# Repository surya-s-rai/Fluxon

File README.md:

# Fluxon
## Project Overview

<br><br>

__Fluxon__ - A PVDF Sensor based Flux logger that collects collision data, a especailly designed payload for CubeSat\
Collects useful data values once embedded on side walls of the satellite as shown in the Zine page above.
<br><br>

 ## Why I made this
 I made this project for a hardware hackathon called fallout organised by [Hack Club](https://github.com/hackclub), and particularly choosed to make this Iot device as i wanted to make a prototype of something real used in spacecrafts.
 ## Why it is relevant
 * Scientific value: Current flux models like [ORDEM](https://orbitaldebris.jsc.nasa.gov/modeling/ordem.html) and [MASTER](https://conference.sdo.esoc.esa.int/proceedings/sdc3/paper/92/SDC3-paper92.pdf) rely mainly on simulations and ground based radar data. A physical sensor mounted on small satellite misson measures impact data better than any simulation can replicate.
 * Cost effective: Commercial impact detectors used in experiments cost thousands of dollars, whereas Fluxon is an open source, low cost substitute PCB board.
 * Mechanical compatibility with real CubeSats: The 60mm x 60mm form factor matches the standard face panel dimensions of CubeSat.
 * Solar powered: The SPV1040 maximum power point tracker(MPPT) harvests energy form solar cell and charges the supercapacitor which reduces the burden of holding a separate battery into a small scale satellite.
 * Mass-frequency distribution: This statistically relevant distribution is obtained from the measured peak voltage which is proportional to mechanical impulse delivered on the aluminium face panel.
 * Flux density: The DS3231 which is a highly accurate real time clock(RTC) helps us to measure particle flux in units of particles per area per second. Flux density is meaningful beacause it varies with orbital altitude, inclination and the time of year(the earth's debris envionment is not uniform).
 * Impact direction: If we embed Fluxon on each face panel of CubeSat, we can calculate angular distribution of impact using parameters like time difference between sensor pairs, speed of sound in aluminium (6320 m/s) and known sensor geometry.
 ## How it works
 The payload is mainly divided into 4 major chunks-
 ### 1. Sensor Frontend (Impact Detection Hardware)
Converts tiny charge generted by the peizoelectric sensors into a measurable voltage.

 ### 2. Signal Conditioning
 Gives Amplified, noise reduced input for Microcontroller unit. 

 ### 3. Microcontroller and Firmware
 Processes sensor data and uses specific codes that brigdes the hardware requirements.

 ### 4. Data Storage System
 Uses W25Q128JV to store collected events.

 ## What's inside this folder
 # PCB Files:
 `* flux logger project.kicad_sch`-contains an illustrative layout of parts and wires used in the project

 `* flux logger project.kicad_pcb`\-The actual pcb layout with all components placed and routed

 `* BOM updated1.xlsx`-Bill of materials with all parts

 # Firware:
 `* Firmware` folder contains hardware specific C codes for parts to operate
 
 # Other files
 `* Flux logger project.kicad_pro`-links `kicad_sch` and `kicad_pcb` files.
 
 `ChargeAmplifier.kicad_sch`,`TPS_Vin.kicad_sch` and`Thre_comp.Kicad_sch` are sub parts of main schema file i.e. `flux logger project.Kicad_sch` 
 ## Build Guide
 1. Replicate the Repository into your local environment
 
 2. View `flux logger project.kicad_sch`,`flux logger project.kicad_pcb` along with the pcb's 3D View on [Kicad](https://www.kicad.org/)
 
 3. PCB Assembly\
 Solder components in the following order:
 resistors and capacitors,Sensor, ADA4530-1, MSP430, W25Q128JV, Connectors and testpoints

 4. Check High Impedance Areas
 Ensure gaurd ring surrounding Amplifier and Sensor input traces.
 Also, keep sensor input clean and isolated.

 5. Power Supply Check
 Apply 3.3V Supply according to `.kicad_sch` file and verify 3.3V rail across each IC.

 6. Firware Installation

 #### Required Software
 * Visual Studio Code Editor
 * PlatformIO Extension
 * Texas Instruments MSP430 Toolchain

 7. Build and Upload Firware

 * Open Firmware folder and run `pio run` on CLI

 * Use upload Button on PlatformIO in order to upload the programme

## BOM
| Value              | Reference                                  | Footprint                                                                          | Qty | Unit Price     | Total Price    | URL                                                                                                                                                                                                                                                                                                                            |
|--------------------|--------------------------------------------|------------------------------------------------------------------------------------|-----|----------------|----------------|--------------------------------------------------------------------------------------------------------------------------------------------------------------------------------------------------------------------------------------------------------------------------------------------------------------------------------|
| 100nf              | C1,C2,C3,C5,C6,C7,C13,C15,C16              | Capacitor_SMD:C_0805_2012Metric                                                    | 9   | 1rs            | 9rs            | https://projectpoint.in/index.php?route=product/product&product_id=636107122                                                                                                                                                                                                                                                   |
| 1uf                | C17,C12                                    | Capacitor_SMD:C_0805_2012Metric                                                    | 2   | 2.09rs         | 4.18rs         | https://robu.in/product/1uf-1000nf-50v-capacitor-0805-smd-package-pack-of-10/                                                                                                                                                                                                                                                  |
| 10uF               | C9,C11,C8,C18                              | Capacitor_SMD:C_0805_2012Metric                                                    | 4   | 3.44rs         | 13.76rs        | https://robu.in/product/grm21bb31c106me15l-murata-electronics-16v-10uf-%C2%B120-0805-multilayer-ceramic-capacitors-mlcc-smd-smt-rohs/                                                                                                                                                                                          |
| 22uF               | C10,C14                                    | Capacitor_SMD:C_1206_3216Metric                                                    | 2   | 0.98rs         | 1.96rs         | https://robu.in/product/cs3216x5r226m6r3nri-samwha-6-3v-22uf-x5r-%C2%B120-1206-multilayer-ceramic-capacitors-mlcc-smd-smt-rohs/                                                                                                                                                                                                |
| 10pf               | Cf1                                        | Resistor_SMD:R_0603_1608Metric                                                     | 1   | 0.92rs         | 0.92rs         | https://robu.in/product/10pf-0603-surface-mount-multilayer-ceramic-capacitor-pack-of-50/                                                                                                                                                                                                                                       |
| 100mf              | S_Cap1                                     | Capacitor_THT:CP_Radial_D10.0mm_P5.00mm                                            | 1   | 99.00rs        | 99.00rs        | https://robu.in/product/0-1f-5-5v-dip-super-capacitor/                                                                                                                                                                                                                                                                         |
| Conn_01x04         | J1                                         | Connector_PinHeader_2.54mm:PinHeader_1x02_P2.54mm_Vertical                         | 2   | 1.50rs         |         3.00rs | https://ifuturetech.org/product/xh2-54-2p-curved-needle-connector-holder-2-54mm-white/                                                                                                                                                                                                                                         |
| 22uH               | L2                                         | Inductor_SMD:L_7.3x7.3_H4.5                                                        | 1   | 8.00rs         | 8.00rs         | https://robu.in/product/68mm-22%C2%B5h-dip-power-inductor-pack-of-5/?gad_source=4&gad_campaignid=17427802703&gbraid=0AAAAADvLFWcfg8oALnufuCDn7QS7Yxsgw&gclid=CjwKCAjw9NjRBhATEiwA_p2J8UuSwcfA2Lr5wrlX0WQkwEzMOyO9Nd1P-ll7UbZbTWQCKsbAUmGBtxoCC_MQAvD_BwE                                                                       |
| 10K                | RV2                                        | Potentiometer_THT:Potentiometer_Bourns_3296W_Vertical                              | 1   | 14.70rs        | 14.70rs        | https://projectpoint.in/index.php?route=product/product&product_id=1500453261                                                                                                                                                                                                                                                  |
| 4.7K               | R1,R3                                      | Resistor_SMD:R_0805_2012Metric                                                     | 2   | 0.44rs         | 0.88rs         | https://robu.in/product/yageo-4-7k-ohm-1-4w-0805-surface-mount-resistor-pack-of-50/?gad_source=4&gad_campaignid=17427802703&gbraid=0AAAAADvLFWcfg8oALnufuCDn7QS7Yxsgw&gclid=CjwKCAjw9NjRBhATEiwA_p2J8W7dYQrZnCsdsWutgfi2JOE-1O_Ukj8FJljlKnBzD6cBGYgiVhon4hoCGU4QAvD_BwE                                                        |
| 100M               | R2                                         | Resistor_SMD:R_1206_3216Metric                                                     | 1   | 84.75rs        | 84.75rs        | https://srkelectronics.in/product/1-mega-ohm-1206-smd-resistor-cfr-pack-of-100/                                                                                                                                                                                                                                                |
| 470K               | R10                                        | Resistor_SMD:R_0603_1608Metric                                                     | 1   | 8.00rs         | 8.00rs         | https://quartzcomponents.com/products/470k-ohm-0603-package-1-10w-smd-resistor-5-tolerance-pack-of-20-pieces?variant=44678130565354&country=IN&currency=INR&utm_medium=product_sync&utm_source=google&utm_content=sag_organic&utm_campaign=sag_organic&srsltid=AfmBOooqJKQhW7YbzG5QFEy0RA-DWadXqpZfb886LD__9LHmBCOOGl79qMo     |
| 10K                | R5,R8,R4,R11                               | Resistor_SMD:R_1206_3216Metric                                                     | 4   | 0.69rs         |       2.76rs   | https://robu.in/product/10k-ohm-1-4w-1206-surface-mount-chip-resistor-pack-of-100/?gad_source=4&gad_campaignid=17427802703&gbraid=0AAAAADvLFWcfg8oALnufuCDn7QS7Yxsgw&gclid=CjwKCAjw9NjRBhATEiwA_p2J8YndTZpSAUk0yIELKsWgMxWpWZsCg3WXOXNIa_TPXrjVBX5Mqxgn4xoChh0QAvD_BwE                                                         |
| 13.3K              | R6                                         | Resistor_SMD:R_1206_3216Metric                                                     | 1   | 1.70rs         | 1.70rs         | https://projectpoint.in/index.php?route=product/product&product_id=499506064082                                                                                                                                                                                                                                                |
| 47k                | R7                                         | Resistor_SMD:R_1206_3216Metric                                                     | 1   | 1.70rs         | 1.70rs         | https://projectpoint.in/index.php?route=product/product&product_id=501263610758                                                                                                                                                                                                                                                |
| 9.1K               | R9                                         | Resistor_SMD:R_1206_3216Metric                                                     | 1   | 1.70rs         | 1.70rs         | https://projectpoint.in/index.php?route=product/product&product_id=502522332251                                                                                                                                                                                                                                                |
| 220K               | RST1                                       | Resistor_SMD:R_1206_3216Metric                                                     | 1   | 1.70rs         | 1.70rs         | https://projectpoint.in/index.php?route=product/product&product_id=501903421507                                                                                                                                                                                                                                                |
| 100K               | RST2                                       | Resistor_SMD:R_1206_3216Metric                                                     | 1   | 0.79rs         | 0.79rs         | https://robu.in/product/100k-ohm-1-4w-1206-surface-mount-chip-resistor-pack-of-100/?gad_source=4&gad_campaignid=17427802703&gbraid=0AAAAADvLFWcd2632Ty4S6PMw-fukdNsD1&gclid=CjwKCAjwl97RBhBWEiwAa9rbXZb4d1umDK0ptoRG9JBTgPPU3BVFfywxlvYmKyawWVLWZqEBT12_WRoCiUYQAvD_BwE                                                        |
| 1M                 | R_hys1                                     | Resistor_SMD:R_0603_1608Metric                                                     | 1   | 9.00rs         | 9.00rs         | https://quartzcomponents.com/products/yageo-1m-ohm-0603-package-1-10w-smd-resistor-1-tolerance-pack-of-20-pieces?variant=45952342458602&country=IN&currency=INR&utm_medium=product_sync&utm_source=google&utm_content=sag_organic&utm_campaign=sag_organic&srsltid=AfmBOop2TJlavxmk_Py0tepDthLo-4WGt6L3SB3oAG36sDNxWqzsWehiqpk |
| 1K                 | R12                                        | Resistor_SMD:R_1206_3216Metric                                                     | 1   | 0.65rs         | 0.65rs         | https://robu.in/product/1k-ohm-1-4w-1206-surface-mount-chip-resistor-pack-of-100/?gad_source=4&gad_campaignid=17427802703&gbraid=0AAAAADvLFWcd2632Ty4S6PMw-fukdNsD1&gclid=CjwKCAjwl97RBhBWEiwAa9rbXZhhZrsnIQ2GC6qdmROeP4HSg4zL3TrdbdUty2efHun2CRlimZtfgBoCH5kQAvD_BwE                                                          |
| PDVF Sensor        | S1                                         | Connector_JST:JST_PH_B2B-PH-K_1x02_P2.00mm_Vertical                                | 1   | 42rs           | 42rs           | https://www.flyrobo.in/10cm-2pin-jst-male-female-plug-connector-plug?tracking=ads&srsltid=AfmBOorg-c1t1ZMkoyWb0uI_qOGQkm21_S4UDt7C8W2L81626DcfXFoIQn0                                                                                                                                                                          |
| Solar_Cell         | SC2                                        | Connector_JST:JST_PH_B2B-PH-K_1x02_P2.00mm_Vertical                                | 1   | 42rs           | 42rs           | https://www.flyrobo.in/10cm-2pin-jst-male-female-plug-connector-plug?tracking=ads&srsltid=AfmBOorg-c1t1ZMkoyWb0uI_qOGQkm21_S4UDt7C8W2L81626DcfXFoIQn0                                                                                                                                                                          |
| PRTR5V0U2X         | D2                                         | Package_TO_SOT_SMD:SOT-143                                                         | 1   | 84.11rs        | 84.11rs        | https://www.digikey.in/en/products/detail/microchip-technology/MIC5203-5.0YM4-TR/771725                                                                                                                                                                                                                                        |
| W25Q128JVS         | U1                                         | Package_SO:SOIC-8_5.3x5.3mm_P1.27mm                                                | 1   |       223.02rs | 223.02rs       | https://evelta.com/serial-nor-flash-memory-128mbit-8pin-soic/?srsltid=AfmBOop8ij99XVMBrUPP4MTaUBqT3zbdZ3cGI8FHUhDra9BC5HyqyAIr                                                                                                                                                                                                 |
| TLV3501AIDBV       | U3                                         | Package_TO_SOT_SMD:SOT-23-6                                                        | 1   | 336.38rs       | 336.38rs       | https://www.mouser.in/ProductDetail/Texas-Instruments/TLV3501AIDR?qs=m96fseALk3U7ir0PfDMQ%252BA%3D%3D&mgh=1&srsltid=AfmBOor5vJxjcE3nIdmz1dbCXO-Uv17hTZ7m_LMbHJgRObglxWCiYOP0Zco                                                                                                                                                |
| MSP430FR5994IPMR.B | U4                                         | MCU:MSP430FR footprint                                                             | 1   | 929.00rs       | 929.00rs       | https://www.mouser.in/ProductDetail/Texas-Instruments/MSP430FR5994IPMR?qs=dSktwyqbRaUcLErRS51dOQ%3D%3D&mgh=1&srsltid=AfmBOorC_1wTVOKZsgPyuOEpQwWsIM3aE6d3V3cPUSy3F-jRGF3ltK4Pe94                                                                                                                                               |
| ADA4530-1          | U5                                         | Package_SO:SOIC-8_3.9x4.9mm_P1.27mm                                                | 1   | 3579.04rs      | 3579.04rs      | https://www.mouser.in/ProductDetail/Analog-Devices/ADA4530-1ARZ?qs=JeIcUl65ClBv6gT9eb3ViA%3D%3D&mgh=1&srsltid=AfmBOorU-kISNIBcR4dI59y3OOEkDu8qQd61ynzLychaZnXB45u1Smna6m4                                                                                                                                                      |
| DS3231M            | U6                                         | Package_SO:SOIC-16W_7.5x10.3mm_P1.27mm                                             | 1   | 218.00rs       | 218.00rs       | https://robu.in/product/ds3231-ic-real-time-clock-integrated-rtc-tcxo-crystal/?gad_source=4&gad_campaignid=17427802703&gbraid=0AAAAADvLFWcd2632Ty4S6PMw-fukdNsD1&gclid=CjwKCAjw9NjRBhATEiwA_p2J8bUNeLHsm7K7N2HT5aExEh7PZg8PEYmbdlRroAsWpZUMoNvL3sb1choCtCgQAvD_BwE                                                             |
| TPS7A4701xRGW      | U8                                         | Package_DFN_QFN:Texas_RGW0020A_VQFN-20-1EP_5x5mm_P0.65mm_EP3.15x3.15mm_ThermalVias | 1   | 540.76rs       | 540.76rs       | https://www.lioncircuits.com/parts/TPS7A4701RGWR?srsltid=AfmBOopbvZxVMUhUOCdwxvLDpRitcg0Les7a-ZnXqwtRMHtWEGWGjgl7EgQ                                                                                                                                                                                                           |
| SPV1040TTR         | U9                                         | Package_DFN_QFN:SOIC_1040T_STM                                                     | 1   | 342.13rs       | 342.13rs       | https://www.digikey.in/en/products/detail/stmicroelectronics/SPV1040TTR/2672694                                                                                                                                                                                                                                                |
| TesPoint           | TP_3v3, TP_GND1,TP_GND4, TP_SCAP1,TP_COMP1 | TestPoint:TestPoint_Pad_D1.5mm                                                     | 5   | 15.61rs        |       78.08rs  | https://in.element14.com/keystone/5000/test-point-pcb-color-coded/dp/2250281                                                                                                                                                                                                                                                   |
|                    |                                            |                                                                                    |     | TOTAL=         |     6682.68rs  |                                                                                                                                                                                                                                                                                                                                |

  ## Credit
  I thank this project to-\
  [Kicad](https://www.kicad.org/)\
  [HackClub Fallout](https://fallout.hackclub.com)\
  my beloved parents and friends...

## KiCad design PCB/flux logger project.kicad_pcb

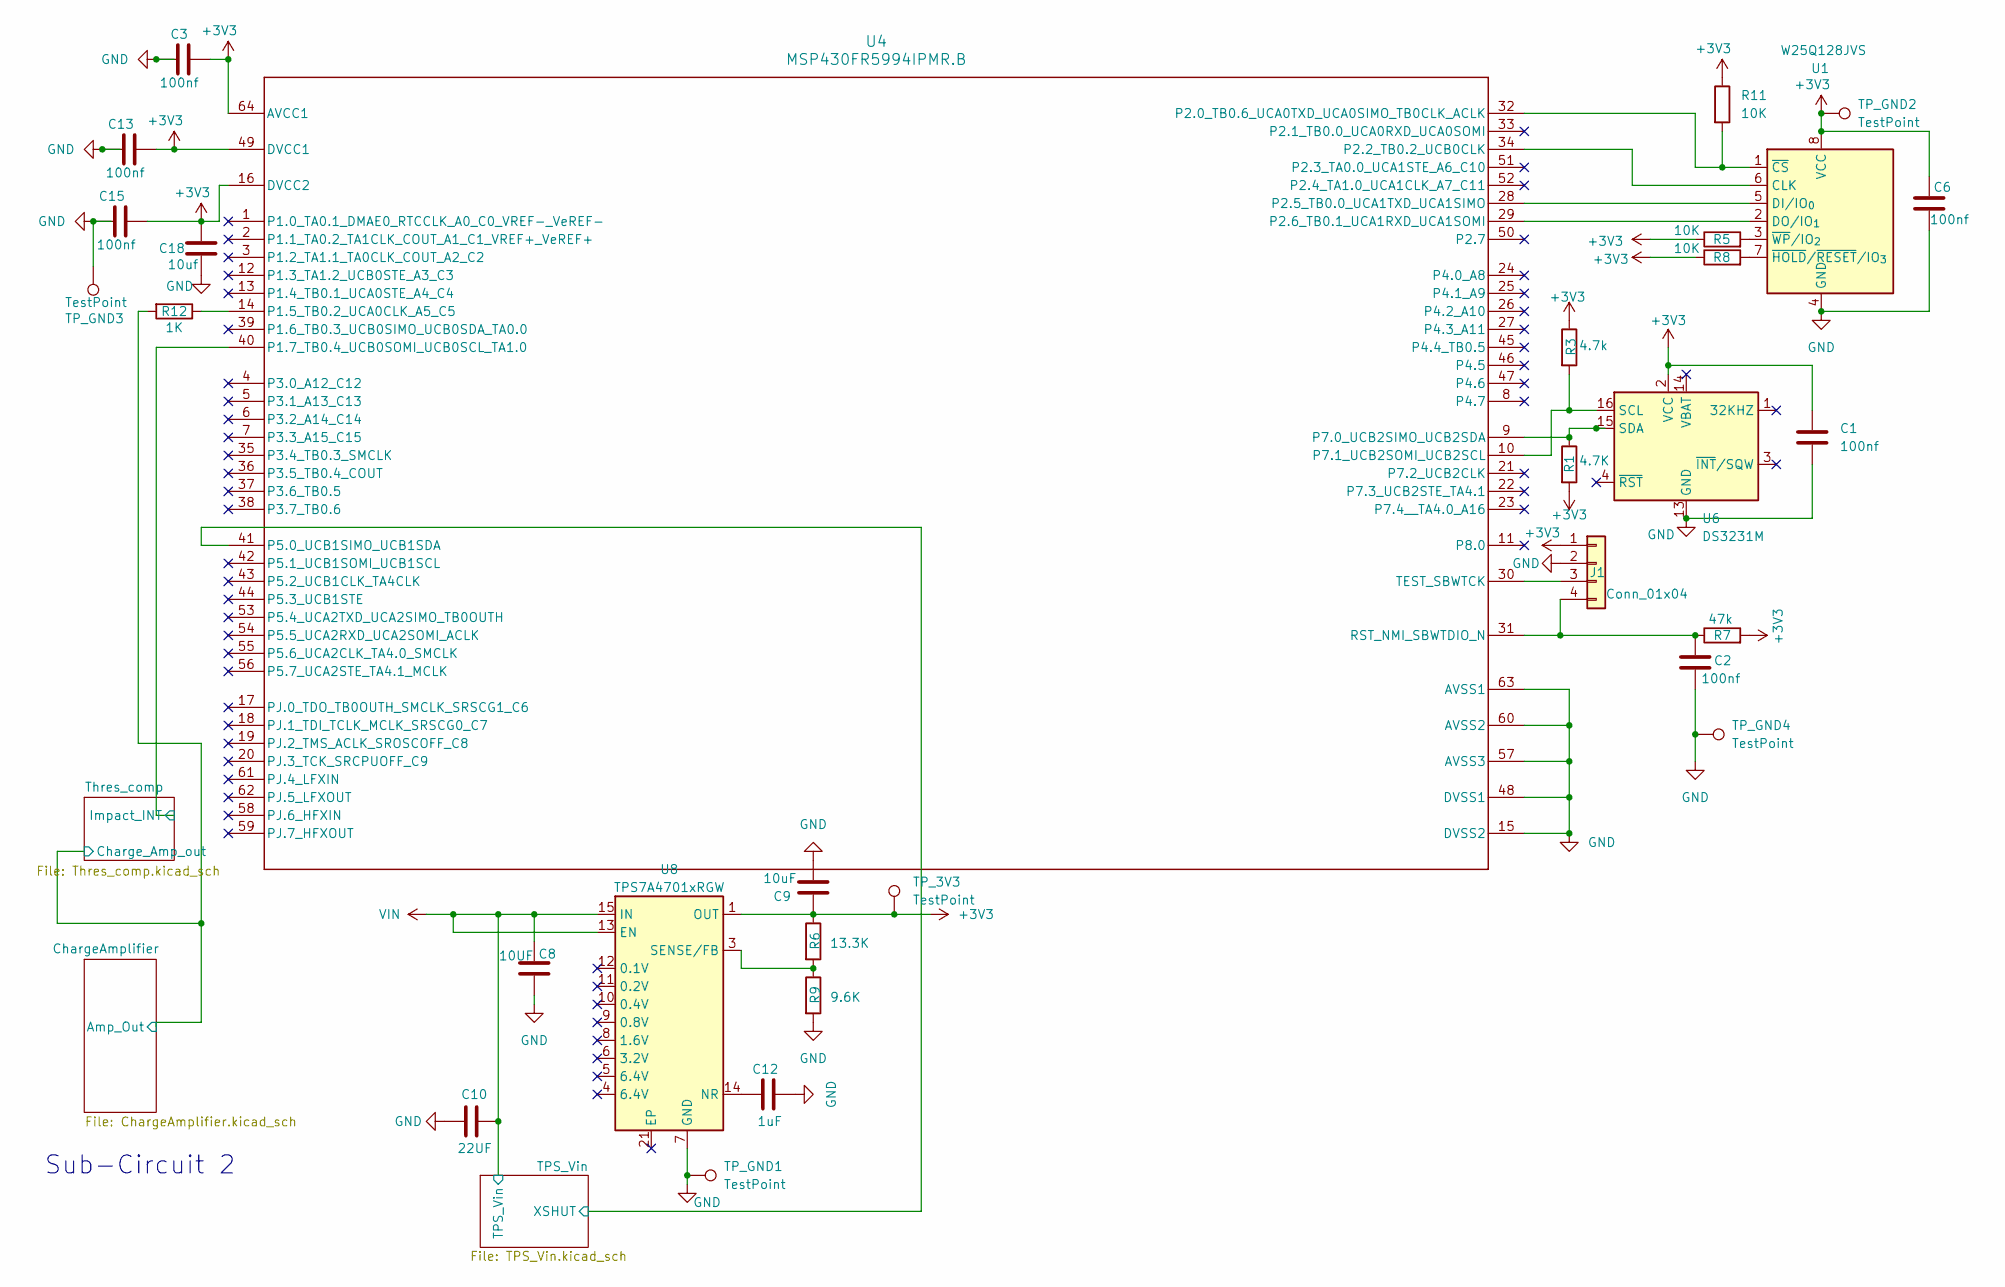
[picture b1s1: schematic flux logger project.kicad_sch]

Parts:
C1, C2, C3, C6, C13, C15: 100nf; C_0805_2012Metric
C8: 10UF; C_0805_2012Metric
C9: 10uF; C_0805_2012Metric
C10: 22UF; C_1206_3216Metric
C12: 1uF; C_0805_2012Metric
C18: 10uf; C_0805_2012Metric
J1: Conn_01x04; PinHeader_1x04_P2.54mm_Vertical
R1: 4.7K; R_0805_2012Metric
R3: 4.7k; R_0805_2012Metric
R5, R8, R11: 10K; R_0805_2012Metric
R6: 13.3K; R_0805_2012Metric
R7: 47k; R_0805_2012Metric
R9: 9.6K; R_0805_2012Metric
R12: 1K; R_0805_2012Metric
TP_3V3: TestPoint; TestPoint_Pad_D1.5mm
TP_GND1, TP_GND2, TP_GND3, TP_GND4: TestPoint; TestPoint_Pad_D1.5mm
U1: W25Q128JVS; SOIC-8_5.3x5.3mm_P1.27mm
U4: MSP430FR5994IPMR.B; MSP430FR footprint
U6: DS3231M; SOIC-16W_7.5x10.3mm_P1.27mm
U8: TPS7A4701xRGW; Texas_RGW0020A_VQFN-20-1EP_5x5mm_P0.65mm_EP3.15x3.15mm_Ther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

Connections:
+3V3: C1.1, C3.2, C6.1, C9.1, C13.2, C15.2, C18.1, J1.1, R1.2, R3.1, R5.1, R6.1, R7.2, R8.1, R11.1, TP_3V3.1 (1_1), TP_GND2.1, U1.8 (VCC), U4.16 (DVCC2), U4.49 (DVCC1), U4.64 (AVCC1), U6.2 (VCC), U8.1 (OUT); also elsewhere on the board
/ChargeAmplifier/Amp_Out: R12.2; also elsewhere on the board
/TPS_Vin/XSHUT: U4.41 (P5.0_UCB1SIMO_UCB1SDA); also elsewhere on the board
/Thres_comp/Impact_INT: U4.40 (P1.7_TB0.4_UCB0SOMI_UCB0SCL_TA1.0); also elsewhere on the board
GND: C1.2, C2.2, C3.1, C6.2, C8.2, C9.2, C10.2, C12.2, C13.1, C15.1, C18.2, J1.2, R9.2, TP_GND1.1 (1_1), TP_GND3.1, TP_GND4.1 (1_1), U1.4 (GND), U4.15 (DVSS2), U4.48 (DVSS1), U4.57 (AVSS3), U4.60 (AVSS2), U4.63 (AVSS1), U6.5 (GND), U6.6 (GND), U6.7 (GND), U6.8 (GND), U6.9 (GND), U6.10 (GND), U6.11 (GND), U6.12 (GND), U6.13 (GND), U8.7 (GND); also elsewhere on the board
unnamed: J1.3, U4.30 (TEST_SBWTCK)
unnamed: C2.1, J1.4, R7.1, U4.31 (RST_NMI_SBWTDIO_N)
unnamed: U1.6 (CLK), U4.34 (P2.2_TB0.2_UCB0CLK)
unnamed: U1.5 (DI/IO_{0}), U4.28 (P2.5_TB0.0_UCA1TXD_UCA1SIMO)
unnamed: U1.2 (DO/IO_{1}), U4.29 (P2.6_TB0.1_UCA1RXD_UCA1SOMI)
unnamed: R11.2, U1.1 (~CS), U4.32 (P2.0_TB0.6_UCA0TXD_UCA0SIMO_TB0CLK_ACLK)
unnamed: R8.2, U1.7 (~HOLD/~RESET/IO_{3})
unnamed: R5.2, U1.3 (~WP/IO_{2})
unnamed: R12.1, U4.14 (P1.5_TB0.2_UCA0CLK_A5_C5)
unnamed: R1.1, U4.9 (P7.0_UCB2SIMO_UCB2SDA), U6.15 (SDA)
unnamed: R3.2, U4.10 (P7.1_UCB2SOMI_UCB2SCL), U6.16 (SCL)
unnamed: C12.1, U8.14 (NR)
unnamed: R6.2, R9.1, U8.3 (SENSE/FB)
VIN: C8.1, C10.1, U8.13 (EN), U8.15 (IN), U8.16 (IN); also elsewhere on the board

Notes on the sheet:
Sub-Circuit 2

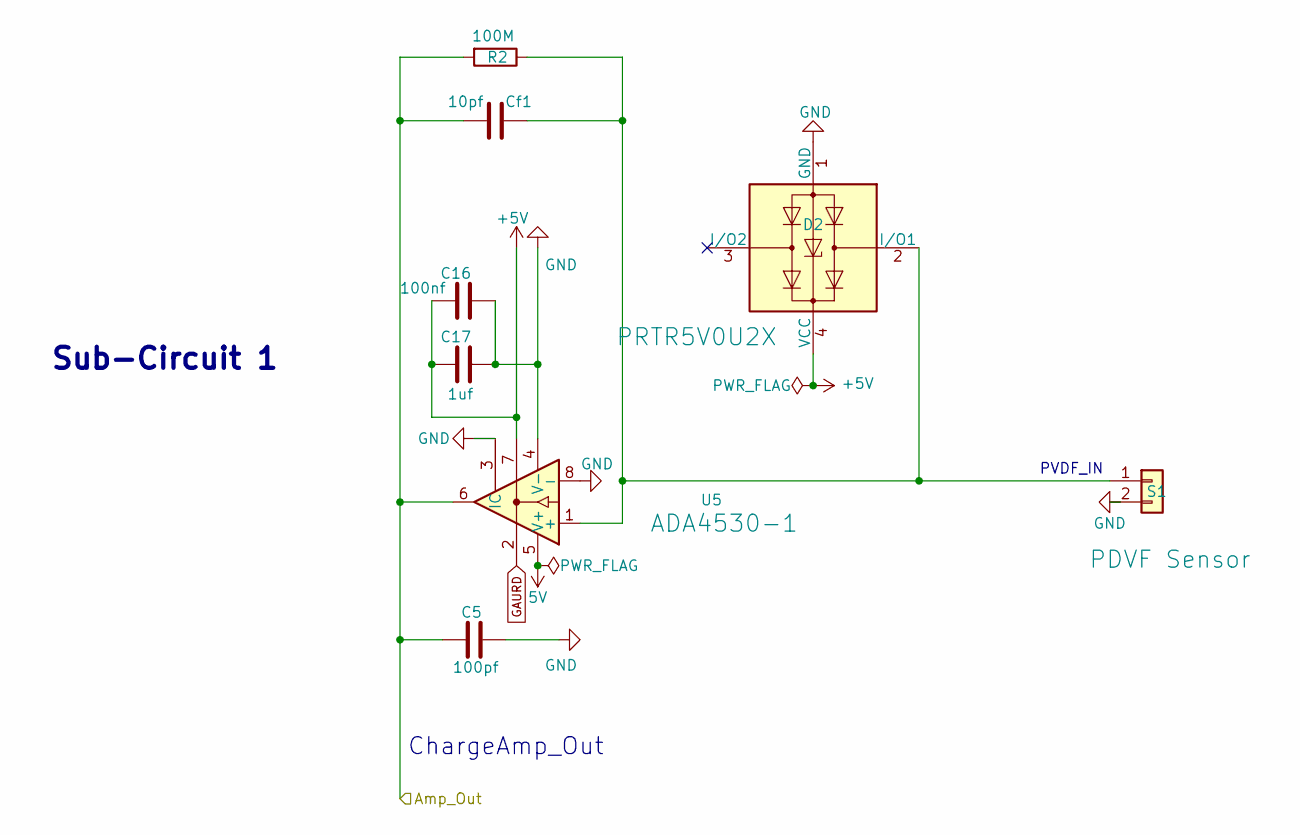
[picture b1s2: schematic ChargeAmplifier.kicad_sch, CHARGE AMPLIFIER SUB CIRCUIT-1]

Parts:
C5: 100pf; C_0805_2012Metric
C16: 100nf; C_0805_2012Metric
C17: 1uf; C_0805_2012Metric
Cf1: 10pf; C_0402_1005Metric
D2: PRTR5V0U2X; SOT-143
R2: 100M; R_1206_3216Metric
S1: PDVF Sensor; JST_PH_B2B-PH-K_1x02_P2.00mm_Vertical
U5: ADA4530-1; SOIC-8_3.9x4.9mm_P1.27mm

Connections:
5V: U5.5 (V+)
+5V: C16.1, C17.1, D2.4 (VCC), U5.7
/ChargeAmplifier/Amp_Out: C5.1, Cf1.2, R2.2, U5.6; also elsewhere on the board
GAURD: U5.2
GND: C5.2, C16.2, C17.2, D2.1 (GND), S1.2, U5.3 (IC), U5.4 (V-), U5.8 (-); also elsewhere on the board
unnamed: Cf1.1, D2.2 (I/O1), R2.1, S1.1, U5.1 (+)

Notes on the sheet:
ChargeAmp_Out
PVDF_IN
Sub-Circuit 1

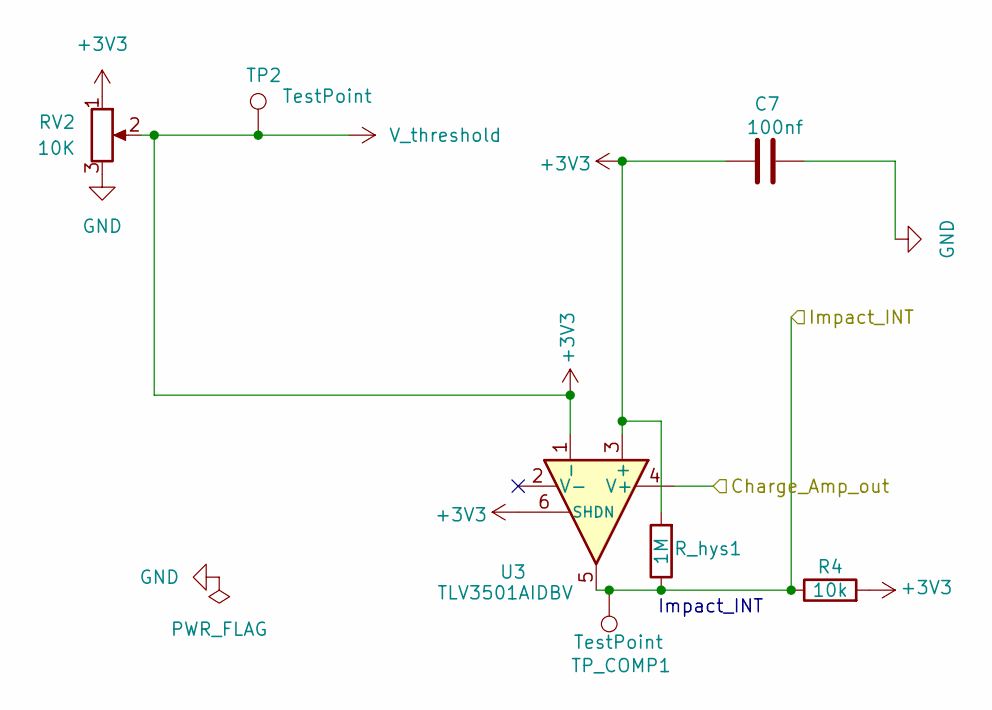
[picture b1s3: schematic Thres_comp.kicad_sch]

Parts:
C7: 100nf; C_0805_2012Metric
R4: 10k; R_0805_2012Metric
RV2: 10K; Potentiometer_Bourns_3296W_Vertical
R_hys1: 1M; R_0805_2012Metric
TP2: TestPoint; TestPoint_Pad_D1.5mm
TP_COMP1: TestPoint; TestPoint_Pad_D1.5mm
U3: TLV3501AIDBV; SOT-23-6

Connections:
+3V3: C7.1, R4.2, RV2.1, RV2.2, R_hys1.2, TP2.1, U3.1 (-), U3.3 (+), U3.6 (SHDN); also elsewhere on the board
/ChargeAmplifier/Amp_Out: U3.4 (V+); also elsewhere on the board
/Thres_comp/Impact_INT: R4.1, R_hys1.1, TP_COMP1.1 (1_1), U3.5; also elsewhere on the board
GND: C7.2, RV2.3; also elsewhere on the board

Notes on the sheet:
Impact_INT

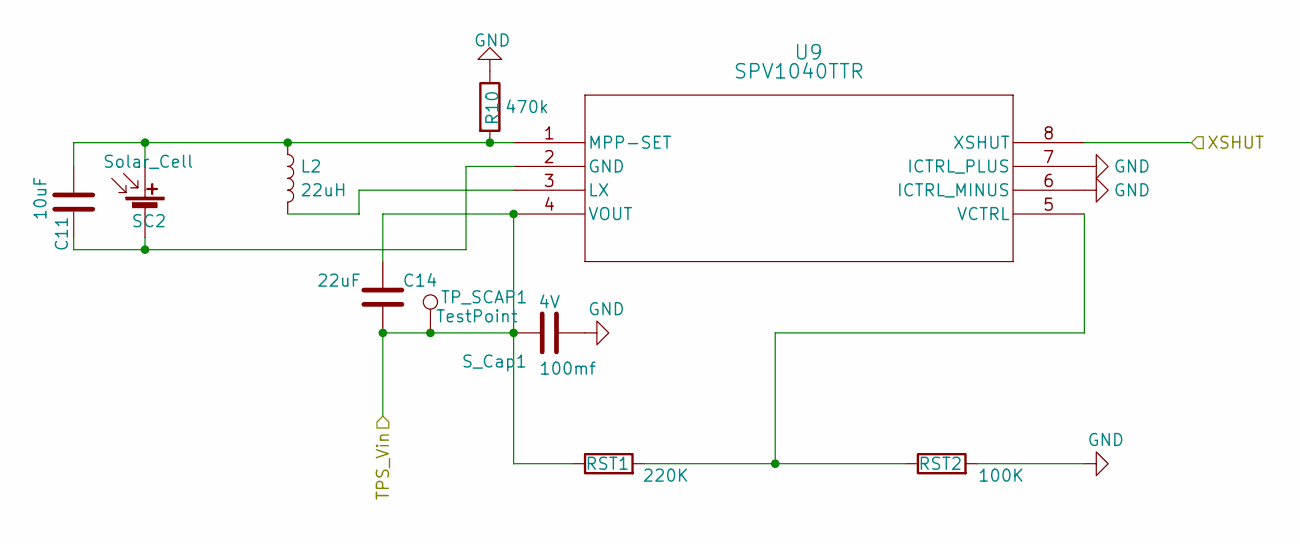
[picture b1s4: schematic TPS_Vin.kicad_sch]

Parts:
C11: 10uF; C_0805_2012Metric
C14: 22uF; C_1206_3216Metric
L2: 22uH; L_7.3x7.3_H4.5
R10: 470k; R_0603_1608Metric
RST1: 220K; R_0612_1632Metric
RST2: 100K; R_0612_1632Metric
SC2: Solar_Cell; JST_PH_B2B-PH-K_1x02_P2.00mm_Vertical
S_Cap1: 100mf; CP_Radial_D10.0mm_P5.00mm; Voltage 4V
TP_SCAP1: TestPoint; TestPoint_Pad_D1.5mm
U9: SPV1040TTR; SOIC_1040T_STM

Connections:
/TPS_Vin/XSHUT: U9.8 (XSHUT); also elsewhere on the board
GND: R10.1, RST2.2, S_Cap1.2, U9.6 (ICTRL_MINUS), U9.7 (ICTRL_PLUS); also elsewhere on the board
unnamed 11: C11.1, L2.1, R10.2, SC2.1 (+), U9.1 (MPP-SET); also elsewhere on the board
unnamed 12: C11.2, SC2.2 (-), U9.2 (GND); also elsewhere on the board
unnamed 24: L2.2, U9.3 (LX); also elsewhere on the board
unnamed: RST1.2, RST2.1, U9.5 (VCTRL)
VIN: C14.1, C14.2, RST1.1, S_Cap1.1, TP_SCAP1.1 (1_1), U9.4 (VOUT); also elsewhere on the board

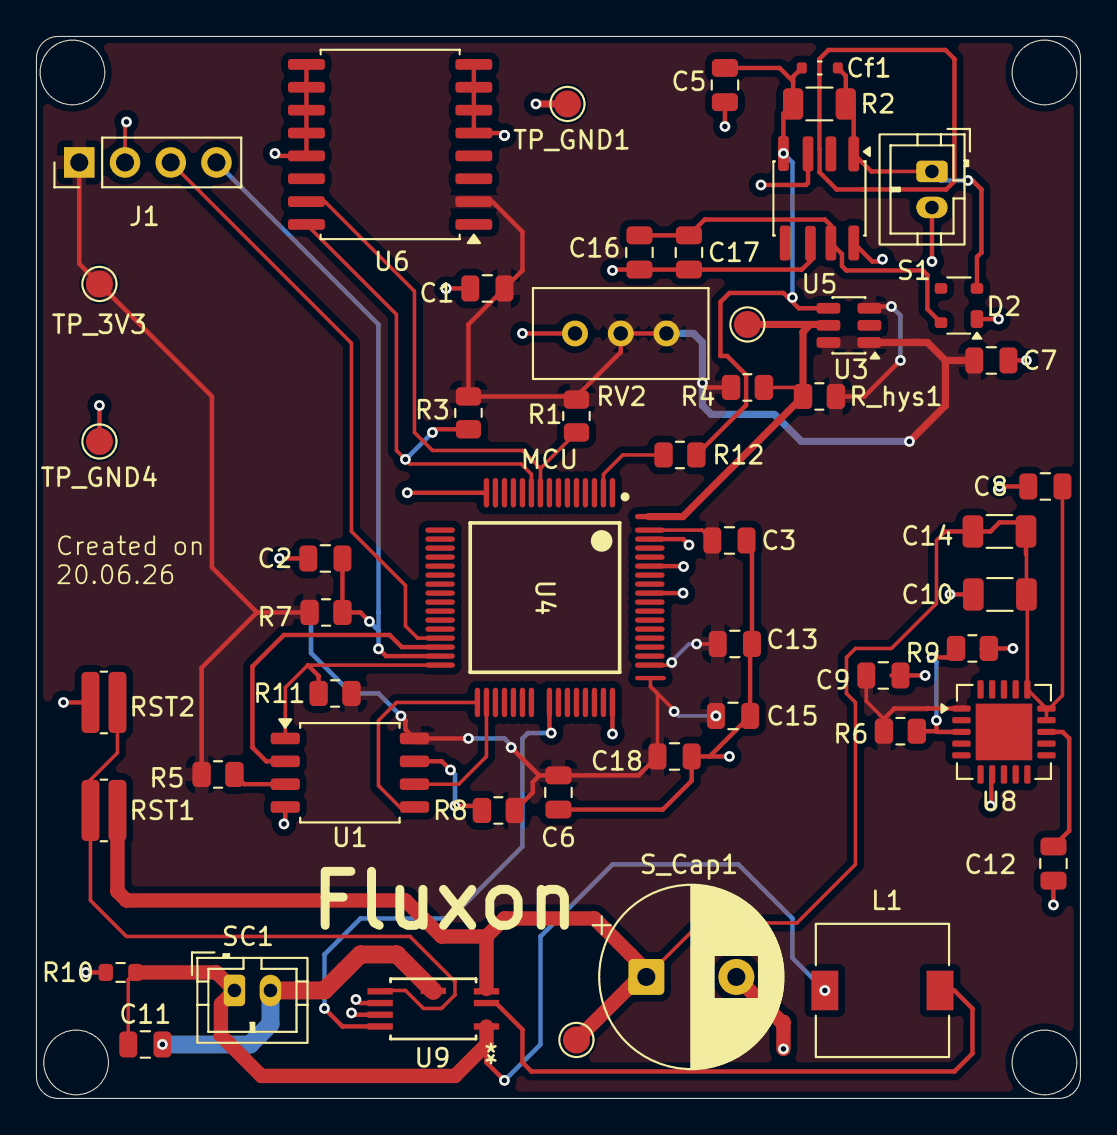
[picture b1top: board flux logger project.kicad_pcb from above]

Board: 2 copper layers, 58.0 x 59.0 mm, 52 parts (0 on the bottom side), 25 nets.

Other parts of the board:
L1: 22uH; L_7.3x7.3_H4.5
SC1: Solar_Cell; JST_PH_B2B-PH-K_1x02_P2.00mm_Vertical

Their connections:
unnamed 11: L1.1, SC1.1 (+); also elsewhere on the board
unnamed 12: SC1.2 (-); also elsewhere on the board
unnamed 24: L1.2; also elsewhere on the board

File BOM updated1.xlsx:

Value | Reference | Footprint | Qty | Unit Price | Total Price | URL
100nf | C1,C2,C3,C5,C6,C7,C13,C15,C16 | Capacitor_SMD:C_0805_2012Metric | 9 | 1rs | 9rs | https://projectpoint.in/index.php?route=product/product&prod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
1uf | C17,C12 | Capacitor_SMD:C_0805_2012Metric | 2 | 2.09rs | 4.18rs | https://robu.in/product/1uf-1000nf-50v-capacitor-0805-smd-pa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
10uF | C9,C11,C8,C18 | Capacitor_SMD:C_0805_2012Metric | 4 | 3.44rs | 13.76rs | https://robu.in/product/grm21bb31c106me15l-murata-electronic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
22uF | C10,C14 | Capacitor_SMD:C_1206_3216Metric | 2 | 0.98rs | 1.96rs | https://robu.in/product/cs3216x5r226m6r3nri-samwha-6-3v-22uf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
10pf | Cf1 | Capacitor_SMD:C_0402_1005Metric | 1 | 0.92rs | 0.92rs | https://robu.in/product/10pf-0603-surface-mount-multilayer-c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
100mf | S_Cap1 | Capacitor_THT:CP_Radial_D10.0mm_P5.00mm | 1 | 99.00rs | 99.00rs | https://robu.in/product/0-1f-5-5v-dip-super-capacitor/
Conn_01x04 | J1 | Connector_PinHeader_2.54mm:PinHeader_1x02_P2.54mm_Vertical | 2 | 1.50rs | 3.00rs | https://ifuturetech.org/product/xh2-54-2p-curved-needle-conn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
22uH | L2 | Inductor_SMD:L_7.3x7.3_H4.5 | 1 | 8.00rs | 8.00rs | https://robu.in/product/68mm-22%C2%B5h-dip-power-inductor-pa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
10K | RV2 | Potentiometer_THT:Potentiometer_Bourns_3296W_Vertical | 1 | 14.70rs | 14.70rs | https://projectpoint.in/index.php?route=product/product&prod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
4.7K | R1,R3 | Resistor_SMD:R_0805_2012Metric | 2 | 0.44rs | 0.88rs | https://robu.in/product/yageo-4-7k-ohm-1-4w-0805-surface-mou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
100M | R2 | Resistor_SMD:R_1206_3216Metric | 1
470K | R10 | Resistor_SMD:R_0603_1608Metric | 1 | 8.00rs | 8.00rs | https://quartzcomponents.com/products/470k-ohm-0603-package-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
10K | R5,R8,R4,R11 | Resistor_SMD:R_1206_3216Metric | 4 | 0.69rs | 2.76rs | https://robu.in/product/10k-ohm-1-4w-1206-surface-mount-chip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
13.3K | R6 | Resistor_SMD:R_1206_3216Metric | 1 | 1.70rs | 1.70rs | https://projectpoint.in/index.php?route=product/product&prod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
47k | R7 | Resistor_SMD:R_1206_3216Metric | 1 | 1.70rs | 1.70rs | https://projectpoint.in/index.php?route=product/product&prod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
9.1K | R9 | Resistor_SMD:R_1206_3216Metric | 1 | 1.70rs | 1.70rs | https://projectpoint.in/index.php?route=product/product&prod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
220K | RST1 | Resistor_SMD:R_1206_3216Metric | 1 | 1.70rs | 1.70rs | https://projectpoint.in/index.php?route=product/product&prod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
100K | RST2 | Resistor_SMD:R_1206_3216Metric | 1
1M | R_hys1 | Resistor_SMD:R_0805_2012Metric | 1
1K | R12 | Resistor_SMD:R_1206_3216Metric | 1
PDVF Sensor | S1 | Connector_JST:JST_PH_B2B-PH-K_1x02_P2.00mm_Vertical | 1 | 8.75rs | 8.75rs | https://sharvielectronics.com/product/jst-ph-2-2-pin-single-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
Solar_Cell | SC2 | Connector_JST:JST_PH_B2B-PH-K_1x02_P2.00mm_Vertical | 1 | 8.75rs | 8.75rs | https://sharvielectronics.com/product/jst-ph-2-2-pin-single-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
PRTR5V0U2X | D2 | Package_TO_SOT_SMD:SOT-143 | 1 | 84.11rs | 84.11rs | https://www.digikey.in/en/products/detail/microchip-technolo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
W25Q128JVS | U1 | Package_SO:SOIC-8_5.3x5.3mm_P1.27mm | 1 | 223.02rs | 223.02rs | https://evelta.com/serial-nor-flash-memory-128mbit-8pin-soic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
TLV3501AIDBV | U3 | Package_TO_SOT_SMD:SOT-23-6 | 1 | 336.38rs | 336.38rs | https://www.mouser.in/ProductDetail/Texas-Instruments/TLV350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
MSP430FR5994IPMR.B | U4 | MCU:MSP430FR footprint | 1 | 1094.87rs | 1094.87rs | https://www.mouser.in/ProductDetail/Texas-Instruments/MSP430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
ADA4530-1 | U5 | Package_SO:SOIC-8_3.9x4.9mm_P1.27mm | 1 | 3579.04rs | 3579.04rs | https://www.mouser.in/ProductDetail/Analog-Devices/ADA4530-1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
DS3231M | U6 | Package_SO:SOIC-16W_7.5x10.3mm_P1.27mm | 1 | 218.00rs | 218.00rs | https://robu.in/product/ds3231-ic-real-time-clock-integrated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
TPS7A4701xRGW | U8 | Package_DFN_QFN:Texas_RGW0020A_VQFN-20-1EP_5x5mm_P0.65mm_EP3.15x3.15mm_ThermalV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 | 1 | 540.76rs | 540.76rs | https://www.lioncircuits.com/parts/TPS7A4701RGWR?srsltid=Afm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
SPV1040TTR | U9 | Package_DFN_QFN:SOIC_1040T_STM | 1 | 342.13rs | 342.14rs | https://www.digikey.in/en/products/detail/stmicroelectronics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
TesPoint | TP_3v3, TP_GND1,TP_GND4, TP_SCAP1,TP_COMP1 | TestPoint:TestPoint_Pad_D1.5mm | 5 | 15.61rs | 78.08rs | https://in.element14.com/keystone/5000/test-point-pcb-color-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

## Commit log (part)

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2026-06-21 added all imp files of this project
2026-06-21 Add image to README
2026-06-21 Create Firmware
2026-06-21 Add initial report for firmware files
2026-06-21 Fix minor grammatical error in Report.md
2026-06-21 Expand README with project details and functionality
    Added a section explaining how the Fluxon payload works, including details on the sensor frontend and signal conditioning.
2026-06-21 Fix HTML encoding in README.md
2026-06-21 Fix spelling error in README.md
    Corrected spelling of 'input' in the Signal Conditioning section.
2026-06-21 Fix typos and enhance clarity in README
    Corrected typos and improved sentence clarity in the README.
2026-06-21 made some changes
2026-06-21 Update README with PCB files and BOM details
    Added PCB files and BOM information to the README.
2026-06-21 Enhance README with PCB and firmware details
    Updated README to include detailed PCB files, firmware instructions, and build guide.
2026-06-21 Fix formatting in firmware installation section
    Correct formatting and spacing in the README for firmware installation instructions.
2026-06-21 Fix formatting for Required Software section in README
2026-06-21 Fix typos and improve formatting in README.md
    Corrected typos and formatting in the README file.
2026-06-21 Add credit section to README
    Added a credit section to acknowledge contributors and resources.
2026-06-21 Fix formatting in credit section of README
    Updated credit section formatting in README.md
2026-06-21 Update README with new image and fix typos
    Added an image to the project overview section and corrected typos.
2026-06-21 Add README.md with project image description
2026-06-25 Add BOM section to README
    Added Bill of Materials (BOM) section with component details.
2026-06-26 Enhance README with project details and corrections
    Updated project description and added details about the Fluxon sensor's functionality and relevance. Improved formatting and corrected typos in the README.
2026-06-26 Fix image alignment in project overview section
    Updated image formatting and added alignment in README.
2026-06-26 Update image in README and correct spelling error
    Updated image source in README and fixed typo.
2026-06-26 Replace project image in README
    Updated project image in README.md.
2026-06-26 Update README with additional project image
    Added a new image to the project overview section.
2026-06-27 Create PCB
2026-06-27 Rename flux logger project.kicad_pcb to PCB/flux logger project.kicad_pcb
2026-06-27 Rename TPS_Vin.kicad_sch to PCB/TPS_Vin.kicad_sch
2026-06-27 Rename ChargeAmplifier.kicad_sch to PCB/ChargeAmplifier.kicad_sch
2026-06-27 Rename Thres_comp.kicad_sch to PCB/Thres_comp.kicad_sch
2026-06-27 Rename flux logger project.kicad_pro to PCB/flux logger project.kicad_pro
2026-06-27 Rename flux logger project.kicad_sch to PCB/flux logger project.kicad_sch
2026-06-27 Create CAD
2026-06-27 Add README for CAD folder describing PCB model
2026-06-27 Add important files description to imp.md
2026-06-27 Rename BOM(CSV).csv to Docs/BOM(CSV).csv
2026-06-27 Rename README.md to Docs/README.md
2026-06-27 Rename Zine_page.pdf to Docs/Zine_page.pdf
2026-06-27 Enhance README with new image of pcb
    Updated README to include a new image and corrected typos.
2026-06-27 Fix typo in 'Firmware Installation' section
2026-06-27 Fix typo in README for 'Firmware' section
    Corrected the spelling of 'Firmware' in the README.
2026-06-27 Fix unit prices in BOM section of README
    Updated unit prices for components in the BOM section.
2026-06-27 Rename BOM file in README
    Updated the bill of materials file name from 'BOM updated1.xlsx' to 'BOM(CSV).csv'.
2026-06-27 Clarify BOM file description in README
    Updated README to clarify BOM file description.
2026-06-27 Update README with new PCB layout image
    Added a new image to the README and updated the PCB layout description.
2026-06-27 Update README with new zine image
    Added a new image to the project overview section and corrected a typo in the project description.
2026-06-27 Rename fallout zine1.png to Zine.png
2026-06-27 Revise BOM with updated prices and links
    Updated BOM with new pricing and URLs for components.
2026-06-28 Add image to README for visual enhancement
    Added an image to the README for better visual representation.
